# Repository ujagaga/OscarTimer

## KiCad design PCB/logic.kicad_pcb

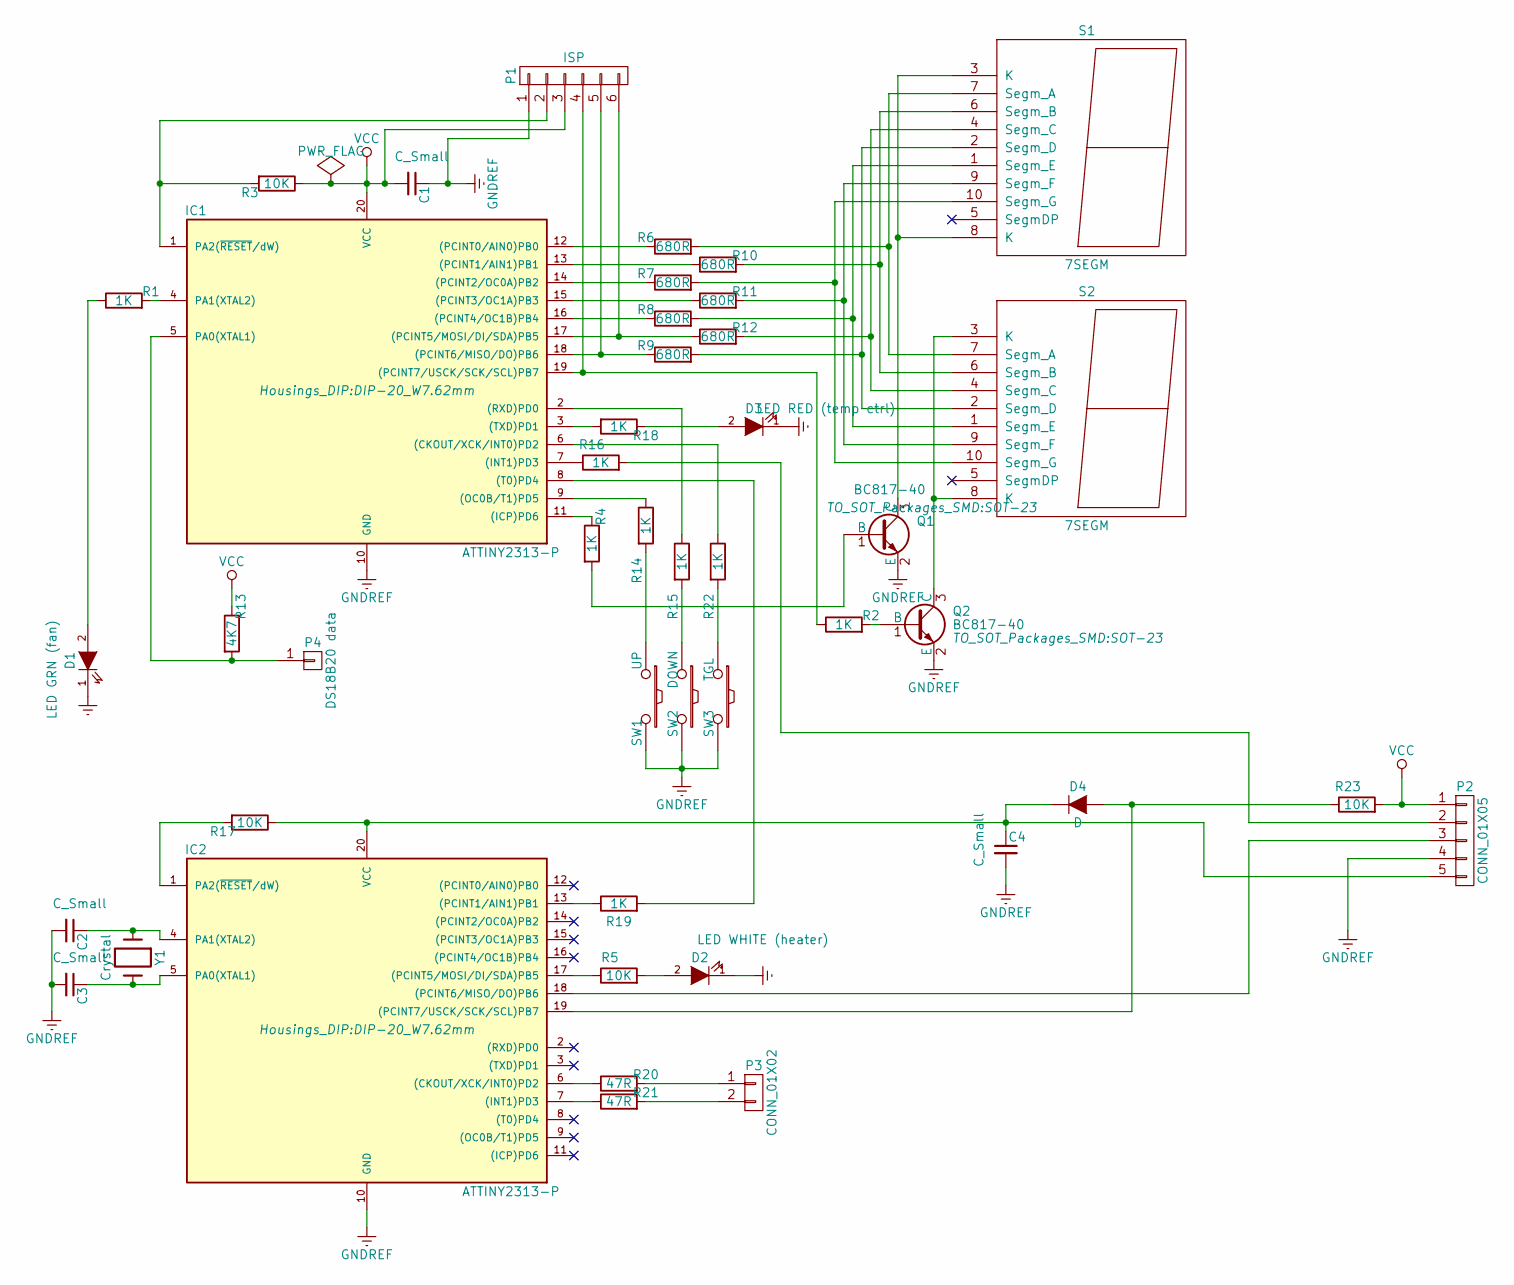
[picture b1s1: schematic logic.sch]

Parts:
C1, C2, C3, C4: C_Small; C_0805_HandSoldering
D1: LED GRN (fan); C_0805_HandSoldering
D2: LED WHITE (heater); C_0805_HandSoldering
D3: LED RED (temp ctrl); C_0805_HandSoldering
D4: D; C_0805_HandSoldering
IC1, IC2: ATTINY2313-P; DIP-20_W7.62mm
P1: ISP; Socket_Strip_Straight_1x06
P2: CONN_01X05; Socket_Strip_Straight_1x05
P3: CONN_01X02; Socket_Strip_Straight_1x02
P4: DS18B20 data; Socket_Strip_Straight_1x01_Pitch1.27mm
Q1, Q2: BC817-40; SOT-23
R1, R2, R4, R14, R15: 1K; R_0805_HandSoldering
R3, R5: 10K; R_0805_HandSoldering
R6, R7, R8, R9, R10, R11, R12: 680R; R_0805_HandSoldering
R13: 4K7; R_0805_HandSoldering
R16, R18, R19, R22: 1K; R_0603_HandSoldering
R17, R23: 10K; R_0603_HandSoldering
R20, R21: 47R; R_0603_HandSoldering
S1, S2: 7SEGM; 7SegmentLED_LTS6760_LTS6780
SW1: UP; Micro_sw_1
SW2: DOWN; Micro_sw_1
SW3: TGL; Micro_sw_1
Y1: Crystal; Crystal_HC49-U_Vertical

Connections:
GNDREF: C1.1, C2.2, C3.2, C4.2, D1.1 (K), D2.1 (K), D3.1 (K), IC1.10 (GND), IC2.10 (GND), P1.1, P2.4, Q1.2 (E), Q2.2 (E), SW1.2, SW2.2, SW3.2
unnamed: C2.1, IC2.4 (PA1(XTAL2)), Y1.1
unnamed: C3.1, IC2.5 (PA0(XTAL1)), Y1.2
unnamed: C4.1, D4.1 (K), IC2.20 (VCC), P2.5, R17.1
unnamed: D1.2 (A), R1.1
unnamed: D2.2 (A), R5.2
unnamed: D3.2 (A), R18.1
unnamed: D4.2 (A), IC2.19 ((PCINT7/USCK/SCK/SCL)PB7), R23.1
unnamed: IC1.1 (PA2(~RESET~/dW)), P1.2, R3.2
unnamed: IC1.2 ((RXD)PD0), R15.1
unnamed: IC1.3 ((TXD)PD1), R18.2
unnamed: IC1.4 (PA1(XTAL2)), R1.2
unnamed: IC1.5 (PA0(XTAL1)), P4.1, R13.2
unnamed: IC1.6 ((CKOUT/XCK/INT0)PD2), R22.1
unnamed: IC1.7 ((INT1)PD3), R16.1
unnamed: IC1.8 ((T0)PD4), R19.2
unnamed: IC1.9 ((OC0B/T1)PD5), R14.1
unnamed: IC1.11 ((ICP)PD6), R4.1
unnamed: IC1.12 ((PCINT0/AIN0)PB0), R6.1
unnamed: IC1.13 ((PCINT1/AIN1)PB1), R10.1
unnamed: IC1.14 ((PCINT2/OC0A)PB2), R7.1
unnamed: IC1.15 ((PCINT3/OC1A)PB3), R11.1
unnamed: IC1.16 ((PCINT4/OC1B)PB4), R8.1
unnamed: IC1.17 ((PCINT5/MOSI/DI/SDA)PB5), P1.6, R12.1
unnamed: IC1.18 ((PCINT6/MISO/DO)PB6), P1.5, R9.1
unnamed: IC1.19 ((PCINT7/USCK/SCK/SCL)PB7), P1.4, R2.1
unnamed: IC2.1 (PA2(~RESET~/dW)), R17.2
unnamed: IC2.6 ((CKOUT/XCK/INT0)PD2), R20.1
unnamed: IC2.7 ((INT1)PD3), R21.1
unnamed: IC2.13 ((PCINT1/AIN1)PB1), R19.1
unnamed: IC2.17 ((PCINT5/MOSI/DI/SDA)PB5), R5.1
unnamed: IC2.18 ((PCINT6/MISO/DO)PB6), P2.3
unnamed: P2.2, R16.2
unnamed: P3.1, R20.2
unnamed: P3.2, R21.2
unnamed: Q1.1 (B), R4.2
unnamed: Q1.3 (C), S1.3 (K), S1.8 (K)
unnamed: Q2.1 (B), R2.2
unnamed: Q2.3 (C), S2.3 (K), S2.8 (K)
unnamed: R6.2, S1.7 (Segm_A), S2.7 (Segm_A)
unnamed: R7.2, S1.10 (Segm_G), S2.10 (Segm_G)
unnamed: R8.2, S1.1 (Segm_E), S2.1 (Segm_E)
unnamed: R9.2, S1.2 (Segm_D), S2.2 (Segm_D)
unnamed: R10.2, S1.6 (Segm_B), S2.6 (Segm_B)
unnamed: R11.2, S1.9 (Segm_F), S2.9 (Segm_F)
unnamed: R12.2, S1.4 (Segm_C), S2.4 (Segm_C)
unnamed: R14.2, SW1.1
unnamed: R15.2, SW2.1
unnamed: R22.2, SW3.1
VCC: C1.2, IC1.20 (VCC), P1.3, P2.1, R3.1, R13.1, R23.2

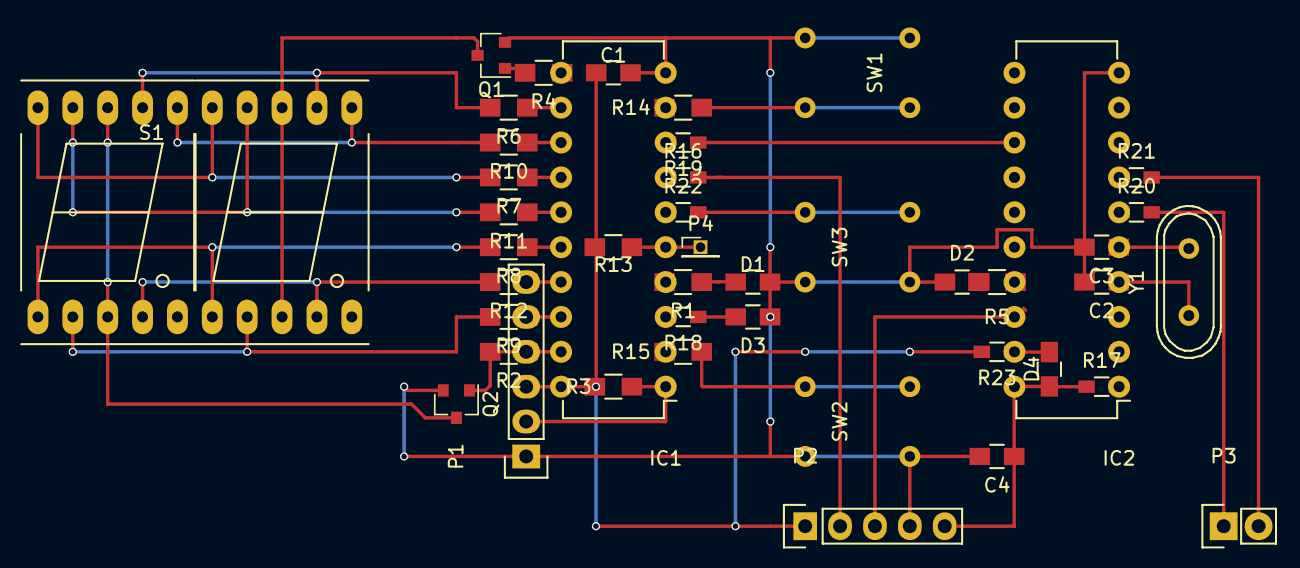
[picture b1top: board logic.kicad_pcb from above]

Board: 2 copper layers, 45 parts (0 on the bottom side), 50 nets.

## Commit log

2017-02-05 Schematic and logic PCB finished
2017-02-05 Changed the schematic to be on only one board
